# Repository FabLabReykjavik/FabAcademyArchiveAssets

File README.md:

# FabAcademyArchiveAssets
All files and assets from the Fab Academy Archive

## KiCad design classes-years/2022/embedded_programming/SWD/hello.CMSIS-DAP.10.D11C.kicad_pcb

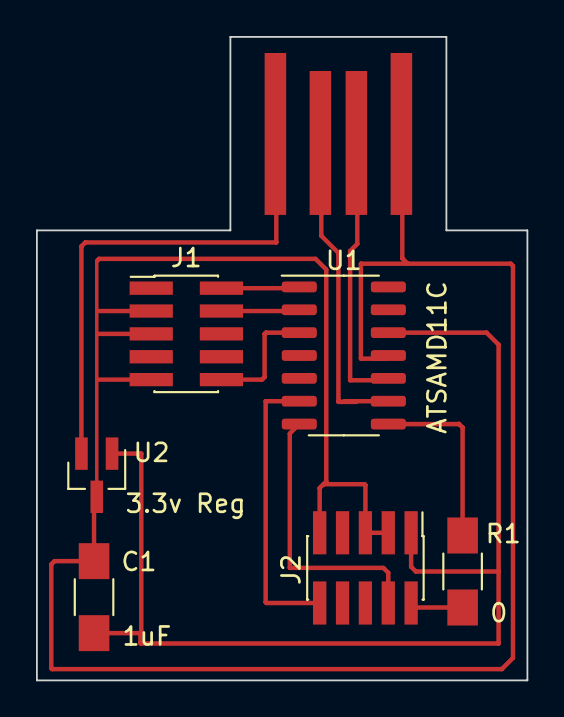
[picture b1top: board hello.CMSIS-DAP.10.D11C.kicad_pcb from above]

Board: 2 copper layers, 27.2 x 35.8 mm, 7 parts (0 on the bottom side), 11 nets.

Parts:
C1: 1uF; C_1206
J1, J2: Conn_PinHeader_2x05_P1.27mm_Vertical_SMD; PinHeader_2x05_P1.27mm_Vertical_SMD
P1: Conn_USB_A_Plain
R1: 0; R_1206
U1: ATSAMD11C; SOIC-14_3.9x8.7mm_P1.27mm
U2: 3.3v Reg; SOT-23

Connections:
CLK: J2.4, U1.7 (PA30/SWCLK)
DIO: J2.2, R1.1, R1.2, U1.8 (PA31/SWDIO)
PA05: J1.2, U1.1 (PA05)
PA08: J1.4, U1.2 (PA08/XIN)
PA09: J1.10, U1.3 (PA09/XOUT)
PA24: P1.2 (D-), U1.9 (PA24)
PA25: P1.3 (D+), U1.10 (PA25)
PWR_3V3: C1.1, J2.1, U1.12 (VDD), U2.1 (VO)
PWR_5V: P1.1 (5V), U2.2 (VI)
PWR_GND: C1.2, J1.3, J1.5, J1.9, J2.3, J2.5, J2.9, P1.4 (GND), U1.11 (GND), U2.3 (GND)
RST: J2.10, U1.6 (PA28/~RST)

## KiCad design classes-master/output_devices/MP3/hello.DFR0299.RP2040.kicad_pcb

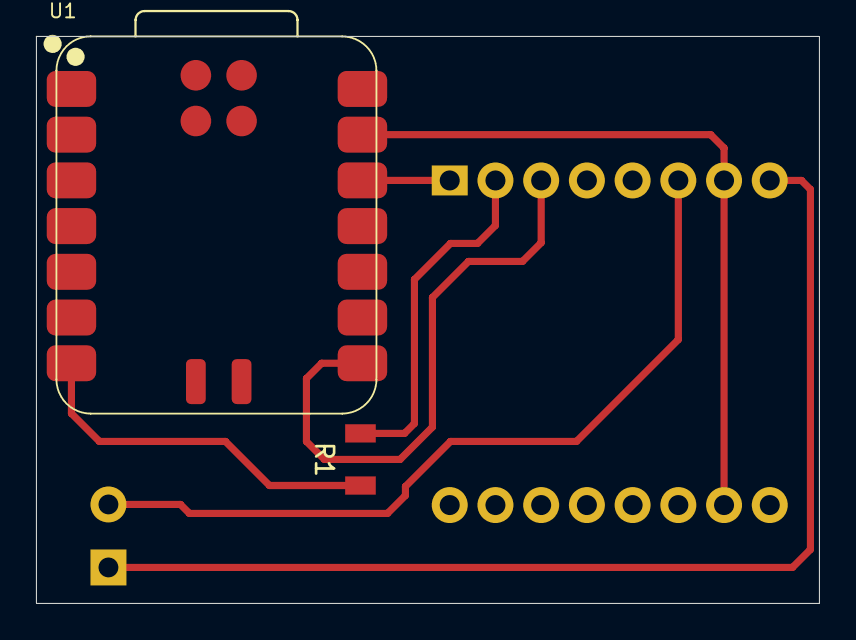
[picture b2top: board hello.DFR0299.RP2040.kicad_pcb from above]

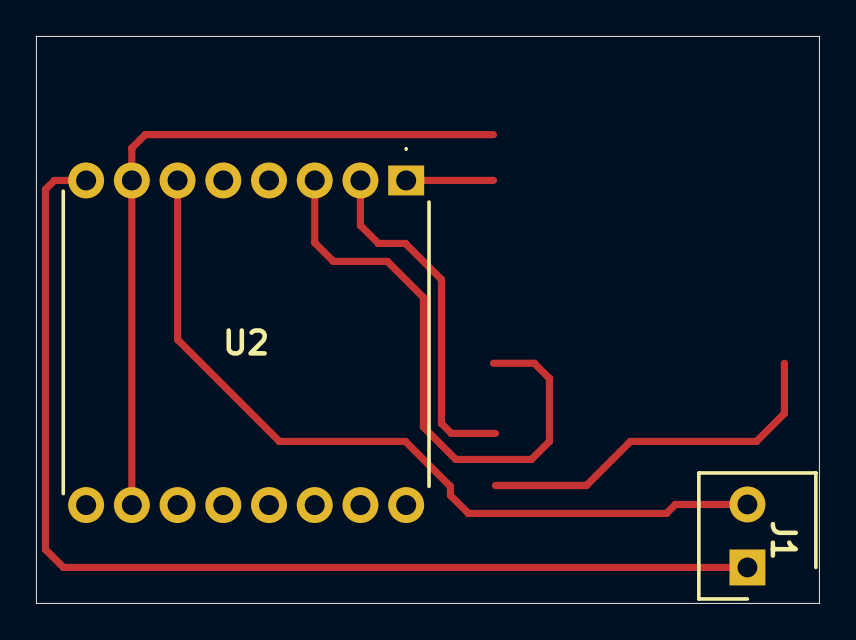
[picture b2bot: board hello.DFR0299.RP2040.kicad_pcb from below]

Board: 2 copper layers, 43.5 x 31.5 mm, 4 parts (2 on the bottom side), 7 nets.

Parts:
J1: ED555_2DS; screw terminal 2
R1: 1k; Resistor 1206
U1: XIAO-RP2040; XIAO-RP2040-SMD
U2: DFR0299; DFR0299 MP3

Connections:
GND: U1.13 (GND), U2.7 (GND_1), U2.10 (GND_2)
unnamed: R1.2, U1.7 (GPIO0/D6/TX)
unnamed: J1.2, U2.6 (SPK1)
unnamed: J1.1, U2.8 (SPK2)
RX: U1.8 (GPIO1/D7/RX), U2.3 (TX)
TX: R1.1, U2.2 (RX)
VCC: U1.12 (VCC_3V3), U2.1 (VCC)

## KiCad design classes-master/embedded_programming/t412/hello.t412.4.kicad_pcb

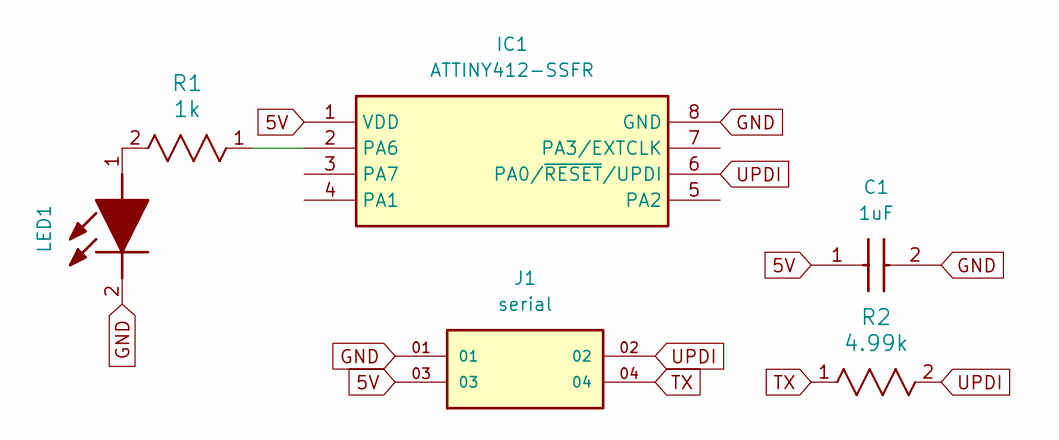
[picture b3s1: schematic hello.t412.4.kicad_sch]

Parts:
C1: 1uF; Resistor 1206; Manufacturer_Part_Number C3216X7R1H105K160AB; Mouser Part Number 810-C3216X7R1H105K
IC1: ATTINY412-SSFR; ATtiny412-SSFR; Manufacturer_Part_Number ATTINY412-SSFR; Mouser Part Number 579-ATTINY412-SSFR
J1: serial; 2x2x0.5 header; PARTREV R; DigiKey_Part_Number SAM8908-ND
LED1: SML-LX1206SRC-TR; LED 1206; Manufacturer_Part_Number SML-LX1206SRC-TR; Mouser Part Number 696-SML-LX1206SRC
R1: 1k; Resistor 1206
R2: 4.99k; Resistor 1206

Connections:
5V: C1.1, IC1.1 (VDD), J1.03
GND: C1.2, IC1.8 (GND), J1.01, LED1.2 (K)
unnamed: IC1.2 (PA6), R1.1
unnamed: LED1.1 (A), R1.2
TX: J1.04, R2.1
UPDI: IC1.6 (PA0/~RESET/UPDI), J1.02, R2.2

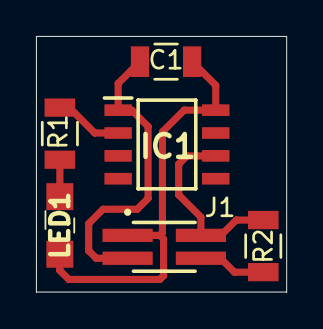
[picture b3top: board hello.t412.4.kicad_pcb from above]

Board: 2 copper layers, 13.9 x 14.2 mm, 6 parts (0 on the bottom side), 6 nets.

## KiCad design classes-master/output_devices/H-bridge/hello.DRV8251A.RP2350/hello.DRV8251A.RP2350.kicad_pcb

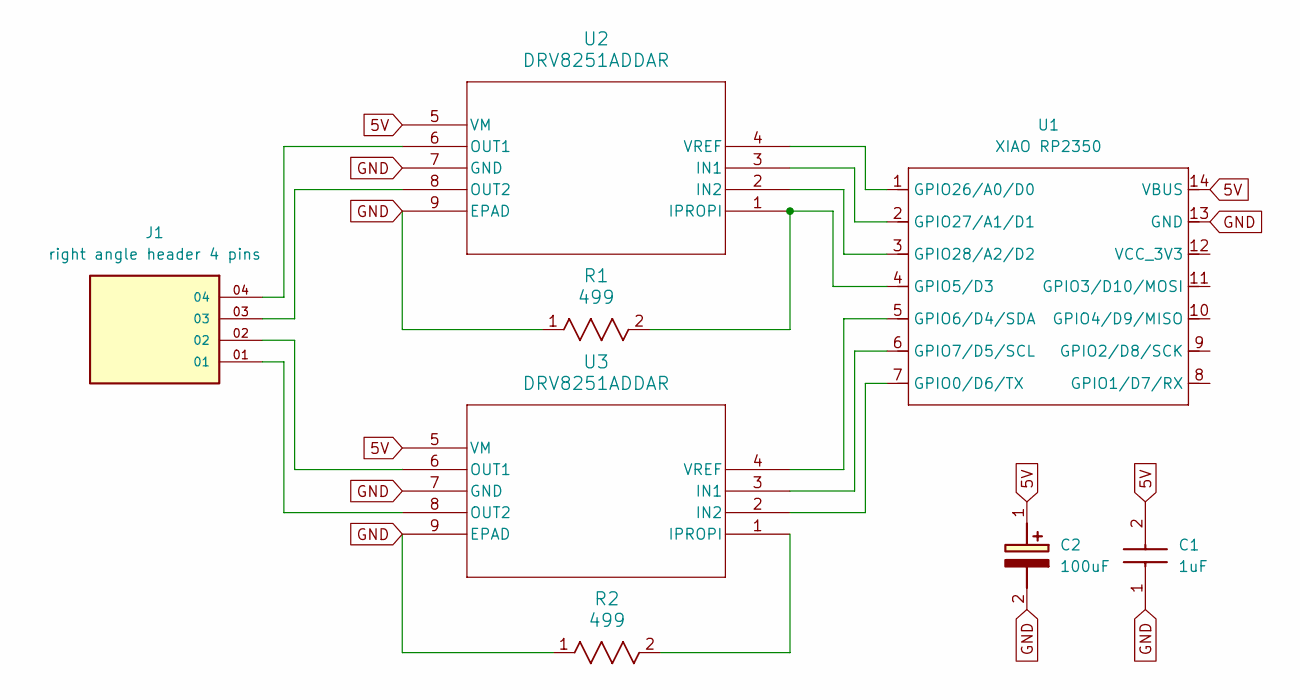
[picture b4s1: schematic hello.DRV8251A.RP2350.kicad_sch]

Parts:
C1: 1uF; Resistor 1206; Manufacturer_Part_Number C3216X7R1H105K160AB; Mouser Part Number 810-C3216X7R1H105K
C2: 100uF; EEEHP1H4R7P; Manufacturer_Part_Number EEE-FN1E101UL; Mouser Part Number 667-EEE-FN1E101UL
J1: right angle header 4 pins; PARTREV R
R1, R2: 499; Resistor 1206
U1: XIAO RP2350; XIAO-RP2350-SMD
U2, U3: DRV8251ADDAR

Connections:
5V: C1.2, C2.1 (+), U1.14 (VBUS), U2.5 (VM), U3.5 (VM)
GND: C1.1, C2.2 (-), R1.1, R2.1, U1.13 (GND), U2.7 (GND), U2.9 (EPAD), U3.7 (GND), U3.9 (EPAD)
unnamed: U1.7 (GPIO0/D6/TX), U3.2 (IN2)
unnamed: R1.2, U1.4 (GPIO5/D3), U2.1 (IPROPI)
unnamed: U1.5 (GPIO6/D4/SDA), U3.4 (VREF)
unnamed: U1.6 (GPIO7/D5/SCL), U3.3 (IN1)
unnamed: U1.1 (GPIO26/A0/D0), U2.4 (VREF)
unnamed: U1.2 (GPIO27/A1/D1), U2.3 (IN1)
unnamed: U1.3 (GPIO28/A2/D2), U2.2 (IN2)
unnamed: J1.04, U2.6 (OUT1)
unnamed: J1.03, U2.8 (OUT2)
unnamed: R2.2, U3.1 (IPROPI)
unnamed: J1.02, U3.6 (OUT1)
unnamed: J1.01, U3.8 (OUT2)

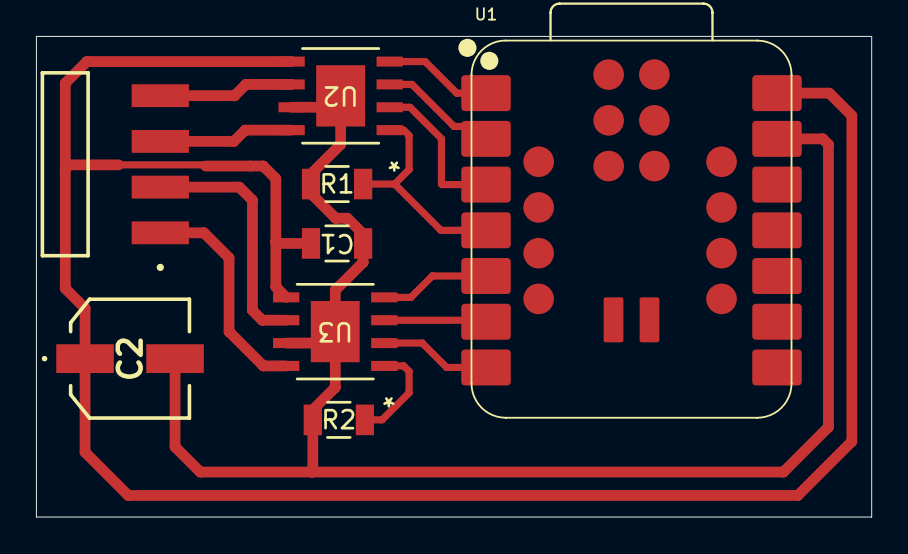
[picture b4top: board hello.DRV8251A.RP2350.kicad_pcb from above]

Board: 2 copper layers, 46.4 x 26.7 mm, 8 parts (0 on the bottom side), 14 nets.

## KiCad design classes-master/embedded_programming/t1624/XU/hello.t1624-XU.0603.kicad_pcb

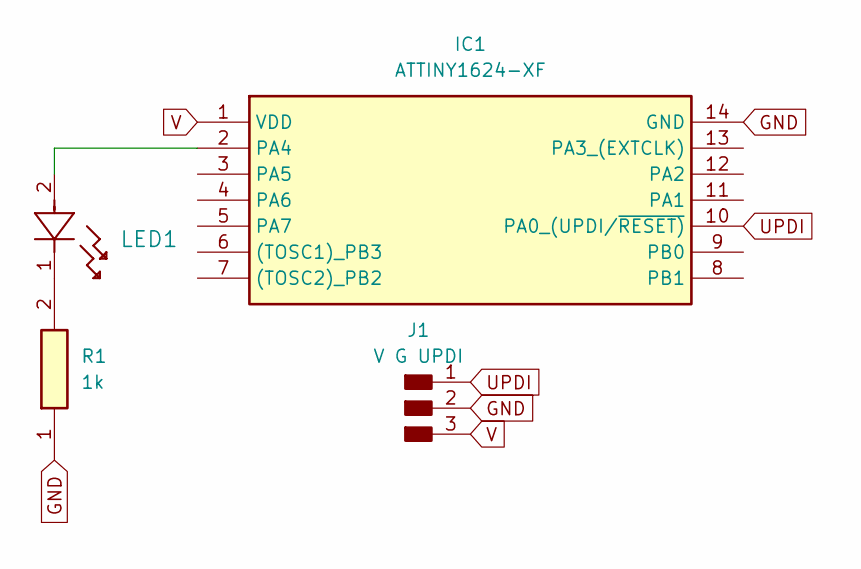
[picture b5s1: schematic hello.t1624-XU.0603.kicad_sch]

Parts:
IC1: ATTINY1624-XF; TSSOP 14; Manufacturer_Part_Number ATTINY1624-XF; Mouser Part Number 556-ATTINY1624-XF
J1: V G UPDI; PinHeader_01x03_P2.54mm_Horizontal_SMD
LED1: LED 0603
R1: 1k; Resistor 0603; Manufacturer_Part_Number RC0603FR-101KL; Mouser Part Number 603-RC0603FR-101KL

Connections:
GND: IC1.14 (GND), J1.2, R1.1
unnamed: IC1.2 (PA4), LED1.2
unnamed: LED1.1, R1.2
UPDI: IC1.10 (PA0_(UPDI/~RESET)), J1.1
V: IC1.1 (VDD), J1.3

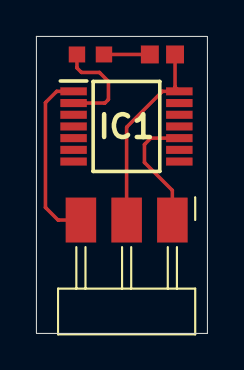
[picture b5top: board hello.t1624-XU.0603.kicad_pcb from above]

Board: 2 copper layers, 9.5 x 16.5 mm, 4 parts (0 on the bottom side), 5 nets.

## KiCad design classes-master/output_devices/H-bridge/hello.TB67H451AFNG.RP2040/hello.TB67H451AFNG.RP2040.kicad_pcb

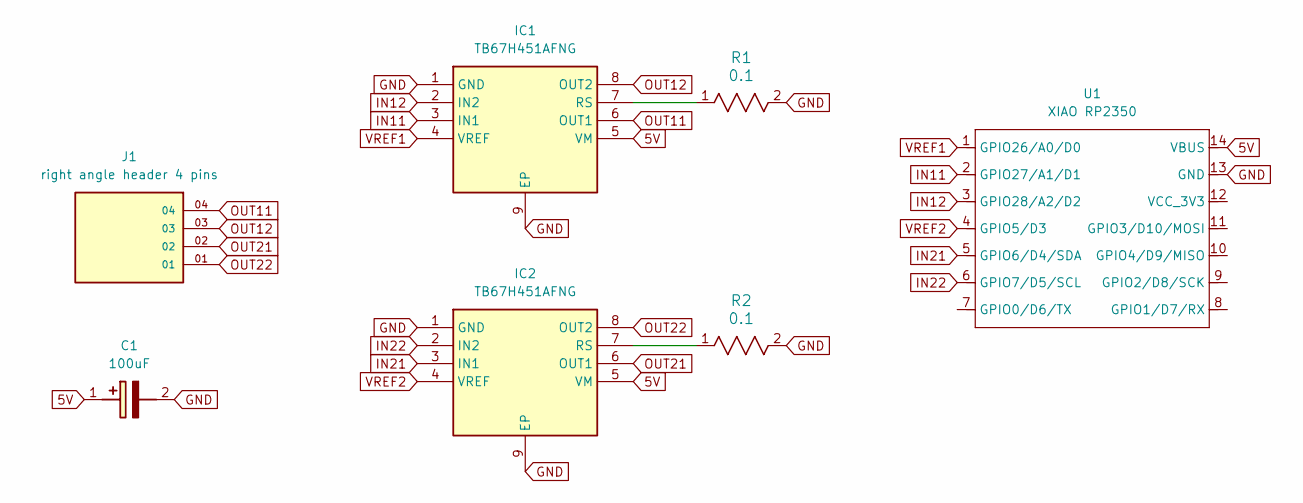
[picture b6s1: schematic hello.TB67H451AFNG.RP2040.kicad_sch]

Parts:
C1: 100uF; EEEHP1H4R7P; Manufacturer_Part_Number EEE-FN1E101UL; Mouser Part Number 667-EEE-FN1E101UL
IC1, IC2: TB67H451AFNG; Manufacturer_Part_Number TB67H451AFNG; Mouser Part Number N/A
J1: right angle header 4 pins; PARTREV R
R1, R2: 0.1; Resistor 1206
U1: XIAO RP2350; XIAO-RP2350-SMD

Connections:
5V: C1.1 (+), IC1.5 (VM), IC2.5 (VM), U1.14 (VBUS)
GND: C1.2 (-), IC1.1 (GND), IC1.9 (EP), IC2.1 (GND), IC2.9 (EP), R1.2, R2.2, U1.13 (GND)
IN11: IC1.3 (IN1), U1.2 (GPIO27/A1/D1)
IN12: IC1.2 (IN2), U1.3 (GPIO28/A2/D2)
IN21: IC2.3 (IN1), U1.5 (GPIO6/D4/SDA)
IN22: IC2.2 (IN2), U1.6 (GPIO7/D5/SCL)
unnamed: IC1.7 (RS), R1.1
unnamed: IC2.7 (RS), R2.1
OUT11: IC1.6 (OUT1), J1.04
OUT12: IC1.8 (OUT2), J1.03
OUT21: IC2.6 (OUT1), J1.02
OUT22: IC2.8 (OUT2), J1.01
VREF1: IC1.4 (VREF), U1.1 (GPIO26/A0/D0)
VREF2: IC2.4 (VREF), U1.4 (GPIO5/D3)

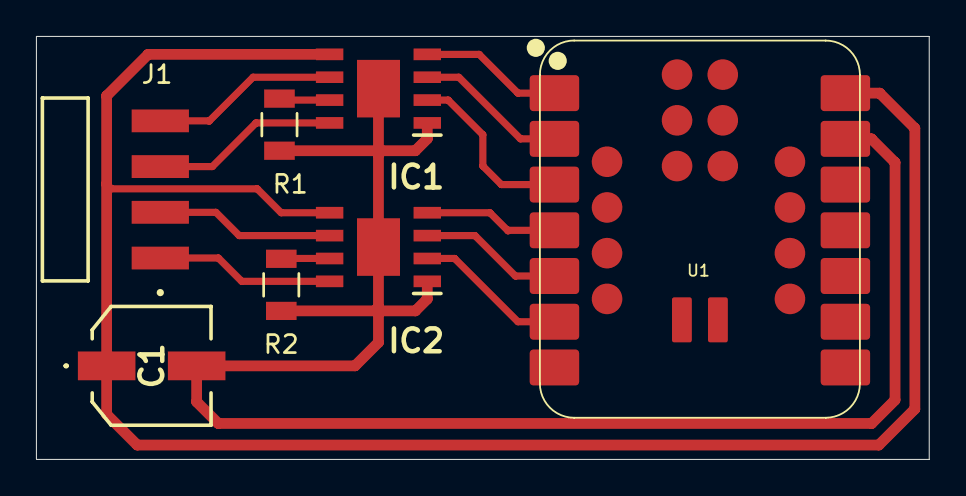
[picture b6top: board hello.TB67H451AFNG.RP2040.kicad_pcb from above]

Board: 2 copper layers, 49.6 x 23.5 mm, 7 parts (0 on the bottom side), 14 nets.

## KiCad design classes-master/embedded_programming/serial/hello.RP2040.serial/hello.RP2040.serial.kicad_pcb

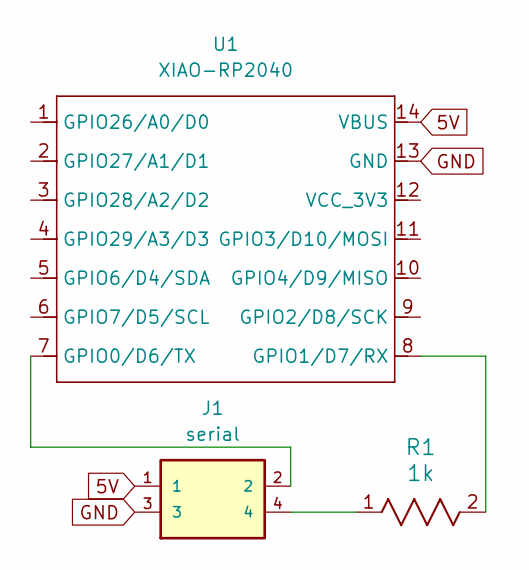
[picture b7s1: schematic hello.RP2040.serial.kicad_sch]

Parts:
J1: serial; 2x2x0.5 header
R1: 1k; Resistor 0603
U1: XIAO-RP2040; XIAO-RP2040-SMD

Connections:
5V: J1.1, U1.14 (VBUS)
GND: J1.3, U1.13 (GND)
unnamed: J1.4, R1.1
unnamed: J1.2, U1.7 (GPIO0/D6/TX)
unnamed: R1.2, U1.8 (GPIO1/D7/RX)

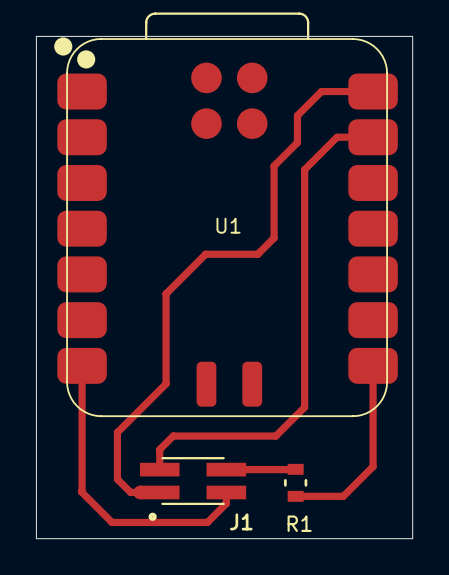
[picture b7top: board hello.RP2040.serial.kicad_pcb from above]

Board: 2 copper layers, 20.9 x 27.9 mm, 3 parts (0 on the bottom side), 5 nets.

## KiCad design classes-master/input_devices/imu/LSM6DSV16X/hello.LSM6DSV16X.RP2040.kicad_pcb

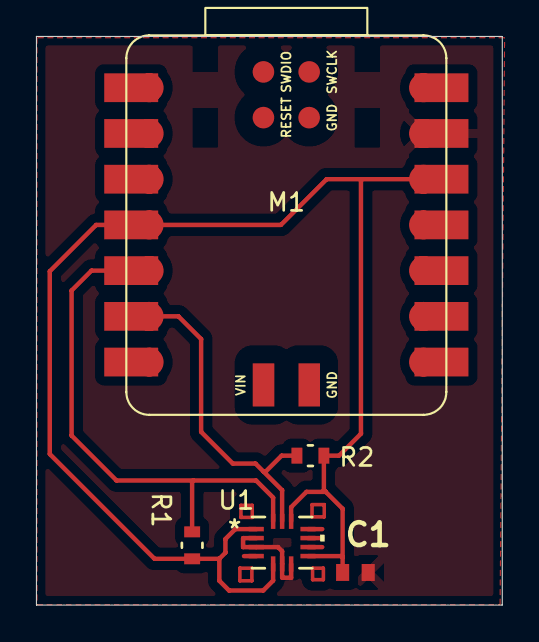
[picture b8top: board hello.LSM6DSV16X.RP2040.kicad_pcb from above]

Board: 2 copper layers, 25.9 x 31.6 mm, 5 parts (0 on the bottom side), 4 nets.

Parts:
C1: 0.1uF; Capacitor 0603
M1: Module_XIAO-RP2040; SeeedStudio_XIAO_RP2040
R1, R2: 10k; Resistor 0603
U1: LSM6DSV16XTR; LGA-14L_STM

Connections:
3V3: C1.1, M1.4 (D3), M1.12 (3V3), R1.2, R2.2, U1.1 (SDO/SA0), U1.5 (VDD_IO), U1.8 (VDD), U1.12 (CS)
GND: C1.2, M1.13 (GND), U1.2 (SDX/AH1/QVAR1), U1.3 (SCX/AH2/QVAR2), U1.6 (GND), U1.7 (GND)
SCL: M1.6 (D5), R2.1, U1.13 (SCL)
SDA: M1.5 (D4), R1.1, U1.14 (SDA)

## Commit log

2025-11-07 all assets from FabAcademy - classes-master - Nov 7 2025
2025-11-10 adding files unique to 2012, 2013, 2014, 2015, 2016
2025-11-10 adding all index.html for 2012, fixing report
2025-11-10 adding all index.html for 2013, fixing report
2025-11-10 adding all index.html for 2014, fixing report
2025-11-10 adding all index.html for 2015, fixing report
2025-11-10 adding all index.html for 2016, fixing report
2025-11-10 adding all index.html for 2017, fixing report
2025-11-10 adding 2018 assets
2025-11-10 adding 2019 assets
2025-11-10 adding 2020
2025-11-10 adding 2021 assets
2025-11-11 adding 2022, 2023, 2024 assets
